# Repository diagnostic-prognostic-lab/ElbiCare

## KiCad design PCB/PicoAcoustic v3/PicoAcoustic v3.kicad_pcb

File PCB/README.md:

# PCB PikoAkustik v3

Revision of **PikoAkustik v2**. Focus: audio quality for audiometry, battery efficiency, and safety.

## Summary

- MCU: STM32F303 → **STM32L4**
- Audio: MAX98357A (Class-D, mono) → **ES8388** (stereo codec: DAC + headphone driver + ADC)
- 5V booster removed
- Relay used for safety and self-test, not for left/right selection
- Main power switch fixed (no leakage current when OFF)

## Changes by block

### Audio
- MAX98357A replaced with **ES8388**
  - Analog output (not PWM), lower noise
  - Stereo: left/right ear selected via I2S data, no relay needed
  - Built-in ADC for calibration self-test
- Audio data 16-bit → **24-bit**
- Added **47 µF coupling capacitors** on LOUT1/ROUT1
- Added **attenuator** (series R + shunt R) per channel: safer maximum level, more accurate low levels
- TRS jack: Tip = L, Ring = R, **Sleeve = GND**
- Removed: L1/L2, speaker filter, MAX98357A gain/SD_MODE setting

### Relay
- G5V-1 (5V coil) → **Omron G6K-2F-Y DC3** (DPDT, 3V coil)
- New function (fail-safe):
  - Relay OFF (default): output to **32 Ω dummy load** + ADC → headphone disconnected, anti-pop, self-test
  - Relay ON: output to headphone (during test)
- Coil powered from 3V3_STM, driven by 2N7002 with B5819W flyback diode

### Power
- **Audio Relay Booster removed** (MCP1640 / MT3608 and related parts)
- Main power switch:
  - Comparator Q3/Q5 (AO3401A) → **BCM857BS** (matched dual PNP)
  - R62/R63 10k → **100k**
  - SW10 moved **before** the ideal diode (VBAT) and **before** D10 (VDDUSB) → near-zero leakage when OFF
- 3 separate AP2112K-3.3 LDOs: STM32, ESP32, codec
- Codec rail: 0 Ω at input (can be replaced with ferrite bead), optional EN from GPIO (DNP)
- L3 (in parallel with LDO) removed
- Label fix: capacitors "4.7uH" → **4.7uF**

### MCU and connectivity
- STM32F303RB → **STM32L4** (SAI for I2S + MCLK, I2C to codec)
- ESP32: added **CH340C USB-UART** + auto-reset (2 NPN), via the charging USB port
- Reset/boot buttons kept (smaller size)
- microSD and SSD1306 OLED unchanged

## Notes

- Dummy load matches the headphone impedance in use (currently 32 Ω, JBL Tune 500)
- Attenuator values are calculated from headphone sensitivity and target maximum level
- Acoustic calibration per headphone is still required; the ADC self-test only checks the electrical path

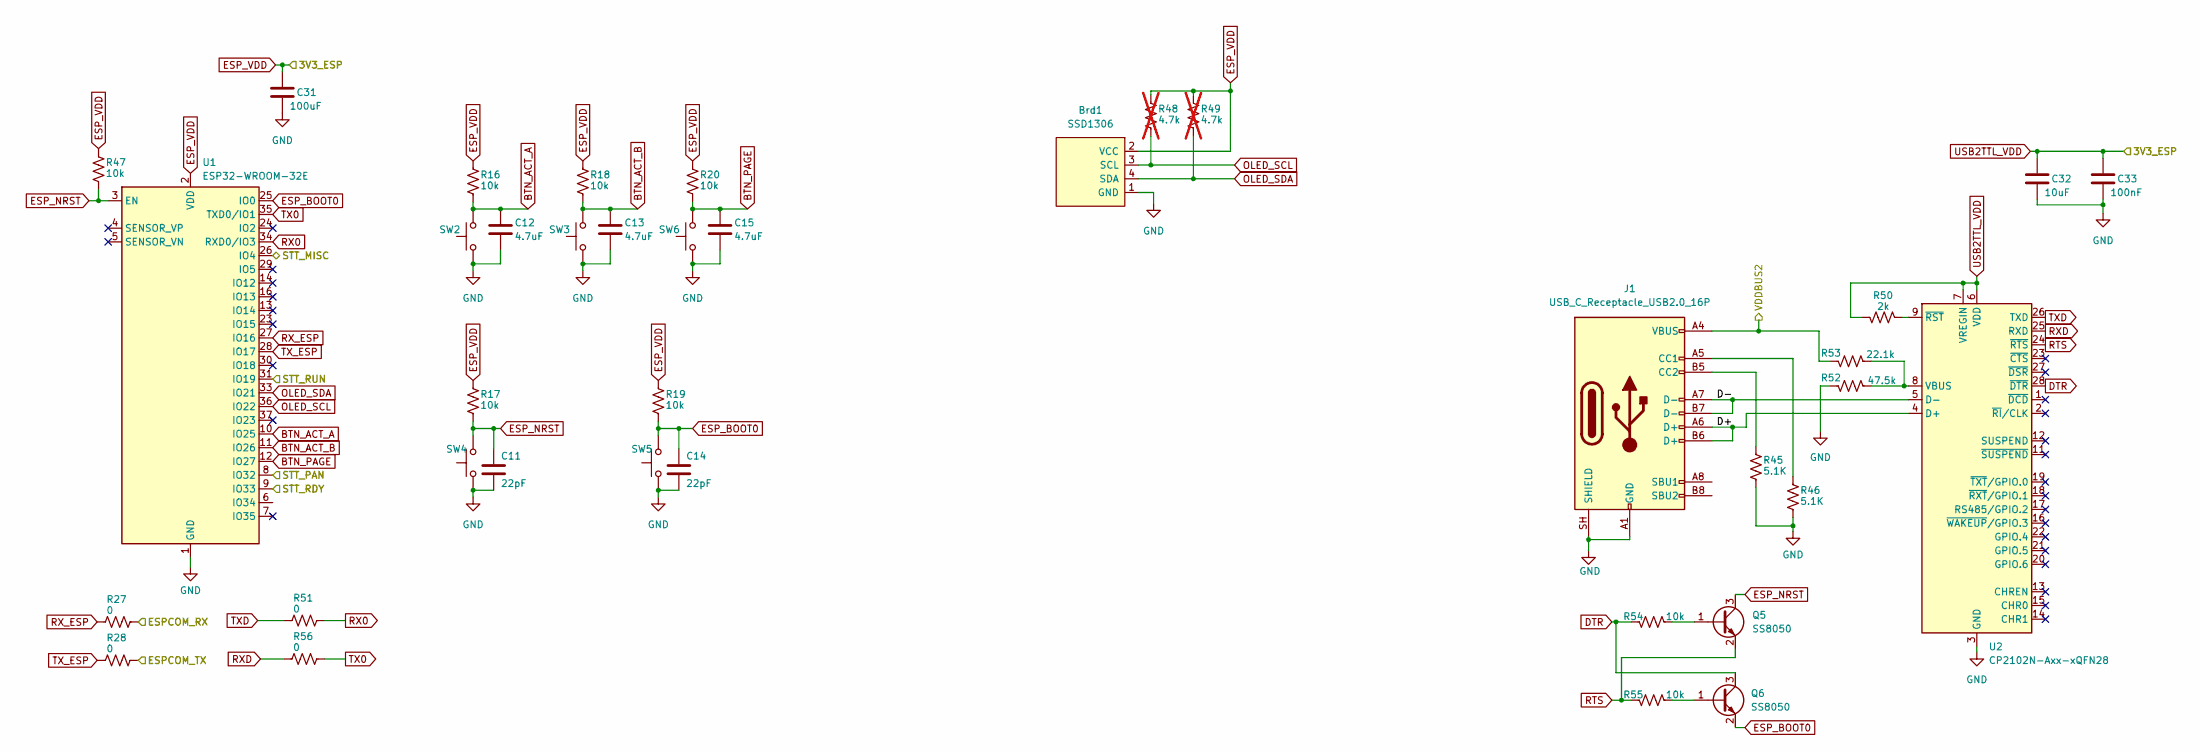
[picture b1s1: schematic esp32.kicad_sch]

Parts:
Brd1: SSD1306; LCD_OLED_128X64_1.3_I2C
C11, C14: 22pF; C_0603_1608Metric
C12, C13, C15: 4.7uF; C_0603_1608Metric
C31: 100uF; C_0603_1608Metric
C32: 10uF; C_0805_2012Metric
C33: 100nF; C_0603_1608Metric
J1: USB_C_Receptacle_USB2.0_16P; USB_C_Receptacle_G-Switch_GT-USB-7010ASV
Q5, Q6: SS8050; SOT-23
R16, R17, R18, R19, R20, R47, R54, R55: 10k; R_0603_1608Metric
R27, R28, R51, R56: 0; R_0603_1608Metric
R45, R46: 5.1K; R_0603_1608Metric
R48, R49: 4.7k; R_0603_1608Metric; not fitted
R50: 2k; R_0603_1608Metric
R52: 47.5k; R_0603_1608Metric
R53: 22.1k; R_0603_1608Metric
SW2, SW3, SW4, SW5, SW6: SW_Push; SW_PUSH_6mm_H13mm
U1: ESP32-WROOM-32E; ESP32-WROOM-32D
U2: CP2102N-Axx-xQFN28; QFN-28-1EP_5x5mm_P0.5mm_EP3.25x3.25mm_ThermalVias

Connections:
/ESP32/D+: J1.A6 (D+), J1.B6 (D+), U2.4 (D+)
/ESP32/D-: J1.A7 (D-), J1.B7 (D-), U2.5 (D-)
/ESP32/ESPCOM_RX: R27.2; also elsewhere on the board
/ESP32/ESPCOM_TX: R28.2; also elsewhere on the board
/ESP32/STT_MISC: U1.26 (IO4); also elsewhere on the board
/ESP32/STT_PAN: U1.8 (IO32); also elsewhere on the board
/ESP32/STT_RDY: U1.9 (IO33); also elsewhere on the board
/ESP32/STT_RUN: U1.31 (IO19); also elsewhere on the board
/ESP32/VDDBUS2: J1.A4 (VBUS), J1.A9 (VBUS), J1.B4 (VBUS), J1.B9 (VBUS), R53.2; also elsewhere on the board
BTN_ACT_A: C12.1, R16.2, SW2.2, U1.10 (IO25)
BTN_ACT_B: C13.1, R18.2, SW3.2, U1.11 (IO26)
BTN_PAGE: C15.1, R20.2, SW6.2, U1.12 (IO27)
DTR: Q6.3 (C), R54.2, U2.28 (~DTR)
ESP_BOOT0: C14.1, Q6.2 (E), R19.2, SW5.2, U1.25 (IO0)
ESP_NRST: C11.1, Q5.3 (C), R17.2, R47.2, SW4.2, U1.3 (EN)
ESP_VDD: Brd1.2 (VCC), C31.1, C32.1, C33.1, R16.1, R17.1, R18.1, R19.1, R20.1, R47.1, R48.1, R49.1, R50.2, U1.2 (VDD), U2.6 (VDD), U2.7 (VREGIN); also elsewhere on the board
GND: Brd1.1 (GND), C11.2, C12.2, C13.2, C14.2, C15.2, C31.2, C32.2, C33.2, J1.A1 (GND), J1.A12 (GND), J1.B1 (GND), J1.B12 (GND), J1.SH (SHIELD), R45.2, R46.2, R52.2, SW2.1, SW3.1, SW4.1, SW5.1, SW6.1, U1.1 (GND), U1.15 (GND), U1.38 (GND), U1.39 (GND), U2.3 (GND), U2.29 (GND); also elsewhere on the board
unnamed: J1.A5 (CC1), R46.1
unnamed: J1.B5 (CC2), R45.1
unnamed: Q5.1 (B), R54.1
unnamed: Q6.1 (B), R55.1
unnamed: R52.1, R53.1, U2.8 (VBUS)
unnamed: R50.1, U2.9 (~RST)
OLED_SCL: Brd1.3 (SCL), R48.2, U1.36 (IO22)
OLED_SDA: Brd1.4 (SDA), R49.2, U1.33 (IO21)
RTS: Q5.2 (E), R55.2, U2.24 (~RTS)
RX0: R51.2, U1.34 (RXD0/IO3)
RXD: R56.1, U2.25 (RXD)
RX_ESP: R27.1, U1.27 (IO16)
TX0: R56.2, U1.35 (TXD0/IO1)
TXD: R51.1, U2.26 (TXD)
TX_ESP: R28.1, U1.28 (IO17)

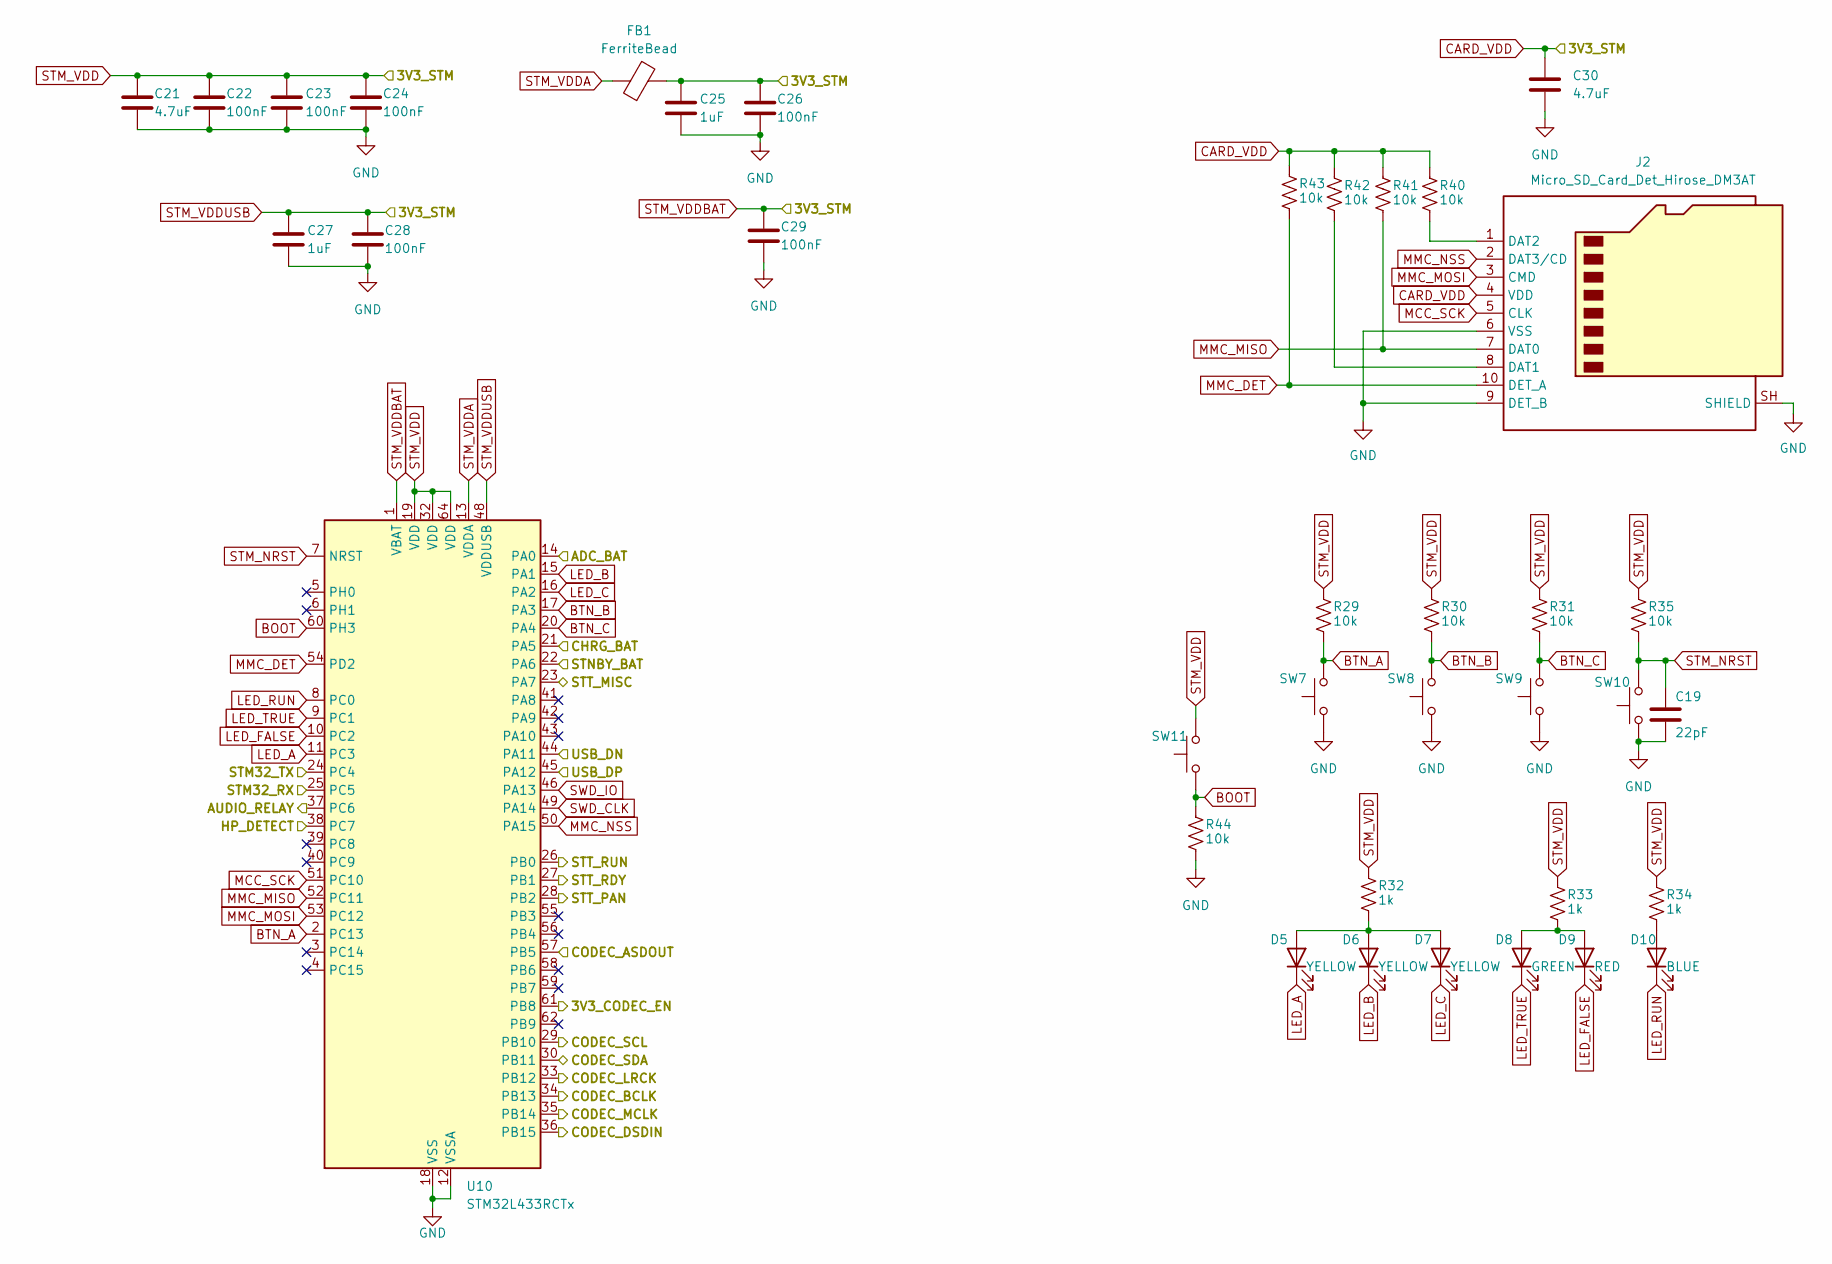
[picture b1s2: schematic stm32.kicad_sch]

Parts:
C19: 22pF; C_0603_1608Metric
C21, C30: 4.7uF; C_0603_1608Metric
C22, C23, C24, C26, C28, C29: 100nF; C_0603_1608Metric
C25, C27: 1uF; C_0603_1608Metric
D5, D6, D7: YELLOW; LED_0603_1608Metric
D8: GREEN; LED_0603_1608Metric
D9: RED; LED_0603_1608Metric
D10: BLUE; LED_0603_1608Metric
FB1: FerriteBead; L_0603_1608Metric
J2: Micro_SD_Card_Det_Hirose_DM3AT; microSD_HC_Hirose_DM3AT-SF-PEJM5
R29, R30, R31, R35, R40, R41, R42, R43, R44: 10k; R_0603_1608Metric
R32, R33, R34: 1k; R_0603_1608Metric
SW7, SW8, SW9, SW10, SW11: SW_Push; SW_PUSH_6mm_H13mm
U10: STM32L433RCTx; LQFP-64_10x10mm_P0.5mm

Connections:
/Analog Line/AUDIO_RELAY: U10.37 (PC6); also elsewhere on the board
/Analog Line/CODEC_ASDOUT: U10.57 (PB5); also elsewhere on the board
/Analog Line/CODEC_DSDIN: U10.36 (PB15); also elsewhere on the board
/Analog Line/CODEC_LRCK: U10.33 (PB12); also elsewhere on the board
/Analog Line/CODEC_MCLK: U10.35 (PB14); also elsewhere on the board
/Analog Line/CODEC_SCL: U10.29 (PB10); also elsewhere on the board
/Analog Line/CODEC_SCLK: U10.34 (PB13); also elsewhere on the board
/Analog Line/CODEC_SDA: U10.30 (PB11); also elsewhere on the board
/Analog Line/HP_DETECT: U10.38 (PC7); also elsewhere on the board
/ESP32/ESPCOM_RX: U10.24 (PC4); also elsewhere on the board
/ESP32/ESPCOM_TX: U10.25 (PC5); also elsewhere on the board
/ESP32/STT_MISC: U10.23 (PA7); also elsewhere on the board
/ESP32/STT_PAN: U10.28 (PB2); also elsewhere on the board
/ESP32/STT_RDY: U10.27 (PB1); also elsewhere on the board
/ESP32/STT_RUN: U10.26 (PB0); also elsewhere on the board
/Power Line/3V3_CODEC_EN: U10.61 (PB8); also elsewhere on the board
/Power Line/STM_DN: U10.44 (PA11); also elsewhere on the board
/Power Line/STM_DP: U10.45 (PA12); also elsewhere on the board
/Power Line/VBAT_SENSE: U10.14 (PA0); also elsewhere on the board
BOOT: R44.1, SW11.1, U10.60 (PH3)
BTN_A: R29.2, SW7.2, U10.2 (PC13)
BTN_B: R30.2, SW8.2, U10.17 (PA3)
BTN_C: R31.2, SW9.2, U10.20 (PA4)
CARD_VDD: C21.1, C22.1, C23.1, C24.1, C25.1, C26.1, C27.1, C28.1, C29.1, C30.1, FB1.2, J2.4 (VDD), R29.1, R30.1, R31.1, R32.1, R33.1, R34.1, R35.1, R40.1, R41.1, R42.1, R43.1, SW11.2, U10.1 (VBAT), U10.19 (VDD), U10.32 (VDD), U10.48 (VDDUSB), U10.64 (VDD); also elsewhere on the board
CHRG: U10.21 (PA5); also elsewhere on the board
GND: C19.2, C21.2, C22.2, C23.2, C24.2, C25.2, C26.2, C27.2, C28.2, C29.2, C30.2, J2.6 (VSS), J2.9 (DET_B), J2.SH (SHIELD), R44.2, SW7.1, SW8.1, SW9.1, SW10.1, U10.12 (VSSA), U10.18 (VSS), U10.31 (VSS), U10.47 (VSS), U10.63 (VSS); also elsewhere on the board
LED_A: D5.1 (K), U10.11 (PC3)
LED_B: D6.1 (K), U10.15 (PA1)
LED_C: D7.1 (K), U10.16 (PA2)
LED_FALSE: D9.1 (K), U10.10 (PC2)
LED_RUN: D10.1 (K), U10.8 (PC0)
LED_TRUE: D8.1 (K), U10.9 (PC1)
MCC_SCK: J2.5 (CLK), U10.51 (PC10)
MMC_DET: J2.10 (DET_A), R43.2, U10.54 (PD2)
MMC_MISO: J2.7 (DAT0), R41.2, U10.52 (PC11)
MMC_MOSI: J2.3 (CMD), U10.53 (PC12)
MMC_NSS: J2.2 (DAT3/CD), U10.50 (PA15)
unnamed: D5.2 (A), D6.2 (A), D7.2 (A), R32.2
unnamed: D8.2 (A), D9.2 (A), R33.2
unnamed: D10.2 (A), R34.2
unnamed: J2.8 (DAT1), R42.2
unnamed: J2.1 (DAT2), R40.2
STM_NRST: C19.1, R35.2, SW10.2, U10.7 (NRST)
STM_VDDA: FB1.1, U10.13 (VDDA)
STNBY: U10.22 (PA6); also elsewhere on the board
SWD_CLK: U10.49 (PA14)
SWD_IO: U10.46 (PA13)

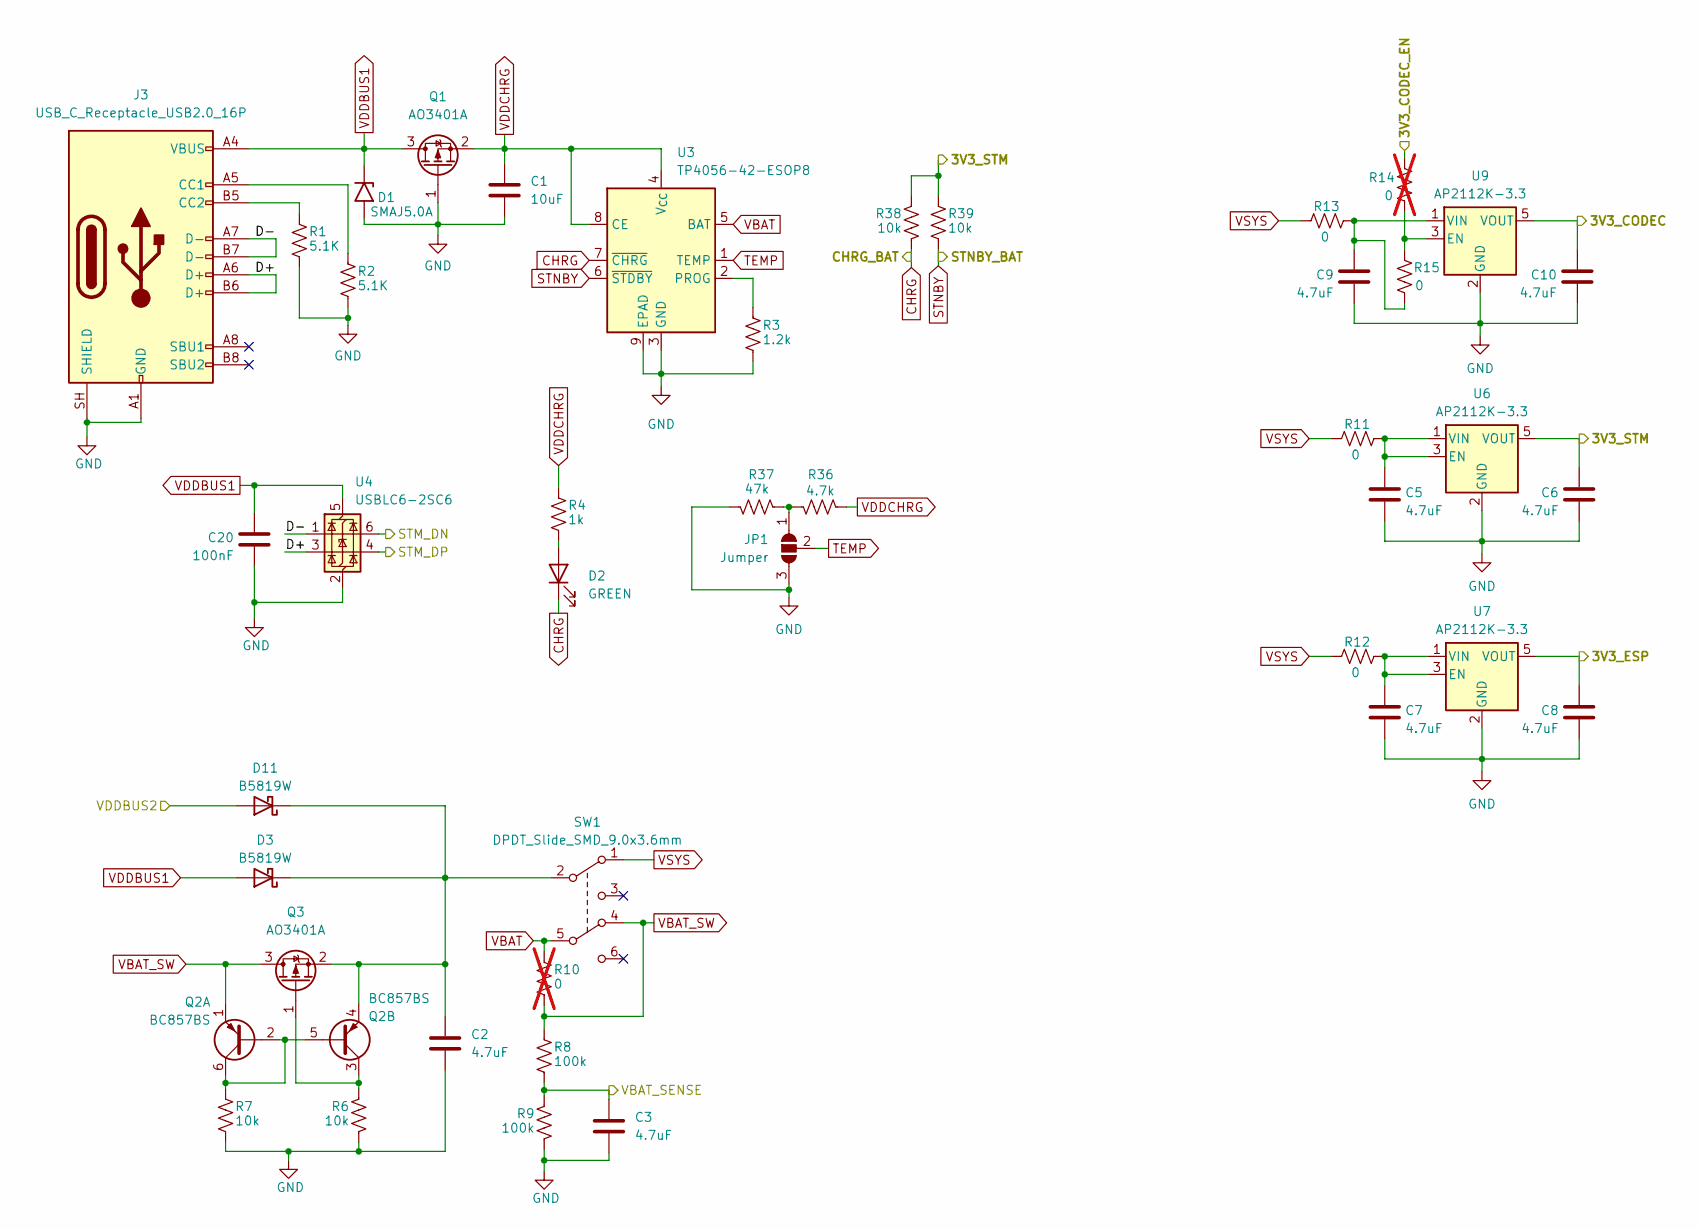
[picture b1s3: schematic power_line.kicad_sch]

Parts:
C1: 10uF; C_0603_1608Metric
C2, C3, C5, C6, C7, C8, C9, C10: 4.7uF; C_0603_1608Metric
C20: 100nF; C_0603_1608Metric
D1: SMAJ5.0A; D_SMA
D2: GREEN; LED_0603_1608Metric
D3, D11: B5819W; D_SMA
J3: USB_C_Receptacle_USB2.0_16P; USB_C_Receptacle_G-Switch_GT-USB-7010ASV
JP1: Jumper; SolderJumper-3_P1.3mm_Open_RoundedPad1.0x1.5mm_NumberLabels
Q1, Q3: AO3401A; SOT-23
Q2: BC857BS; SOT-363_SC-70-6
R1, R2: 5.1K; R_0603_1608Metric
R3: 1.2k; R_0603_1608Metric
R4: 1k; R_0603_1608Metric
R6, R7, R38, R39: 10k; R_0603_1608Metric
R8, R9: 100k; R_0603_1608Metric
R10, R14: 0; R_0603_1608Metric; not fitted
R11, R12, R13, R15: 0; R_0603_1608Metric
R36: 4.7k; R_0603_1608Metric
R37: 47k; R_0603_1608Metric
SW1: DPDT_Slide_SMD_9.0x3.6mm; SW_Push_2P2T_Toggle_CK_PVA2xxH1xxxxxxV2
U3: TP4056-42-ESOP8; SOIC-8-1EP_3.9x4.9mm_P1.27mm_EP2.41x3.3mm_ThermalVias
U4: USBLC6-2SC6; SOT-23-6
U6, U7, U9: AP2112K-3.3; SOT-23-5

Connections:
/ESP32/VDDBUS2: D11.2 (A); also elsewhere on the board
/Power Line/3V3_CODEC_EN: R14.2; also elsewhere on the board
/Power Line/D+: J3.A6 (D+), J3.B6 (D+), U4.3 (I/O2)
/Power Line/D-: J3.A7 (D-), J3.B7 (D-), U4.1 (I/O1)
/Power Line/STM_DN: U4.6 (I/O1); also elsewhere on the board
/Power Line/STM_DP: U4.4 (I/O2); also elsewhere on the board
/Power Line/VBAT_SENSE: C3.1, R8.2, R9.1; also elsewhere on the board
AVDD: C10.1, U9.5 (VOUT); also elsewhere on the board
CARD_VDD: C6.1, R38.1, R39.1, U6.5 (VOUT); also elsewhere on the board
CHRG: D2.1 (K), R38.2, U3.7 (~CHRG); also elsewhere on the board
ESP_VDD: C8.1, U7.5 (VOUT); also elsewhere on the board
GND: C1.2, C2.2, C3.2, C5.2, C6.2, C7.2, C8.2, C9.2, C10.2, C20.2, D1.2 (A2), J3.A1 (GND), J3.A12 (GND), J3.B1 (GND), J3.B12 (GND), J3.SH (SHIELD), JP1.3 (B), Q1.1 (G), R1.2, R2.2, R3.2, R6.2, R7.2, R9.2, R37.2, U3.3 (GND), U3.9 (EPAD), U4.2 (GND), U6.2 (GND), U7.2 (GND), U9.2 (GND); also elsewhere on the board
unnamed: D2.2 (A), R4.2
unnamed: C2.1, D3.1 (K), D11.1 (K), Q2.4 (E2), Q3.2 (S), SW1.2 (B)
unnamed: J3.A5 (CC1), R2.1
unnamed: J3.B5 (CC2), R1.1
unnamed: JP1.1 (A), R36.2, R37.1
unnamed: Q2.2 (B1), Q2.5 (B2), Q2.6 (C1), R7.1
unnamed: Q2.3 (C2), Q3.1 (G), R6.1
unnamed: R3.1, U3.2 (PROG)
unnamed: C5.1, R11.2, U6.1 (VIN), U6.3 (EN)
unnamed: C7.1, R12.2, U7.1 (VIN), U7.3 (EN)
unnamed: R14.1, R15.2, U9.3 (EN)
unnamed: C9.1, R13.2, R15.1, U9.1 (VIN)
STNBY: R39.2, U3.6 (~STDBY); also elsewhere on the board
TEMP: JP1.2 (C), U3.1 (TEMP)
VBAT: R10.1, SW1.5 (B), U3.5 (BAT)
VBAT_SW: Q2.1 (E1), Q3.3 (D), R8.1, R10.2, SW1.4 (A)
VDDBUS1: C20.1, D1.1 (A1), D3.2 (A), J3.A4 (VBUS), J3.A9 (VBUS), J3.B4 (VBUS), J3.B9 (VBUS), Q1.3 (D), U4.5 (VBUS)
VDDCHRG: C1.1, Q1.2 (S), R4.1, R36.1, U3.4 (V_{CC}), U3.8 (CE)
VSYS: R11.1, R12.1, R13.1, SW1.1 (A)

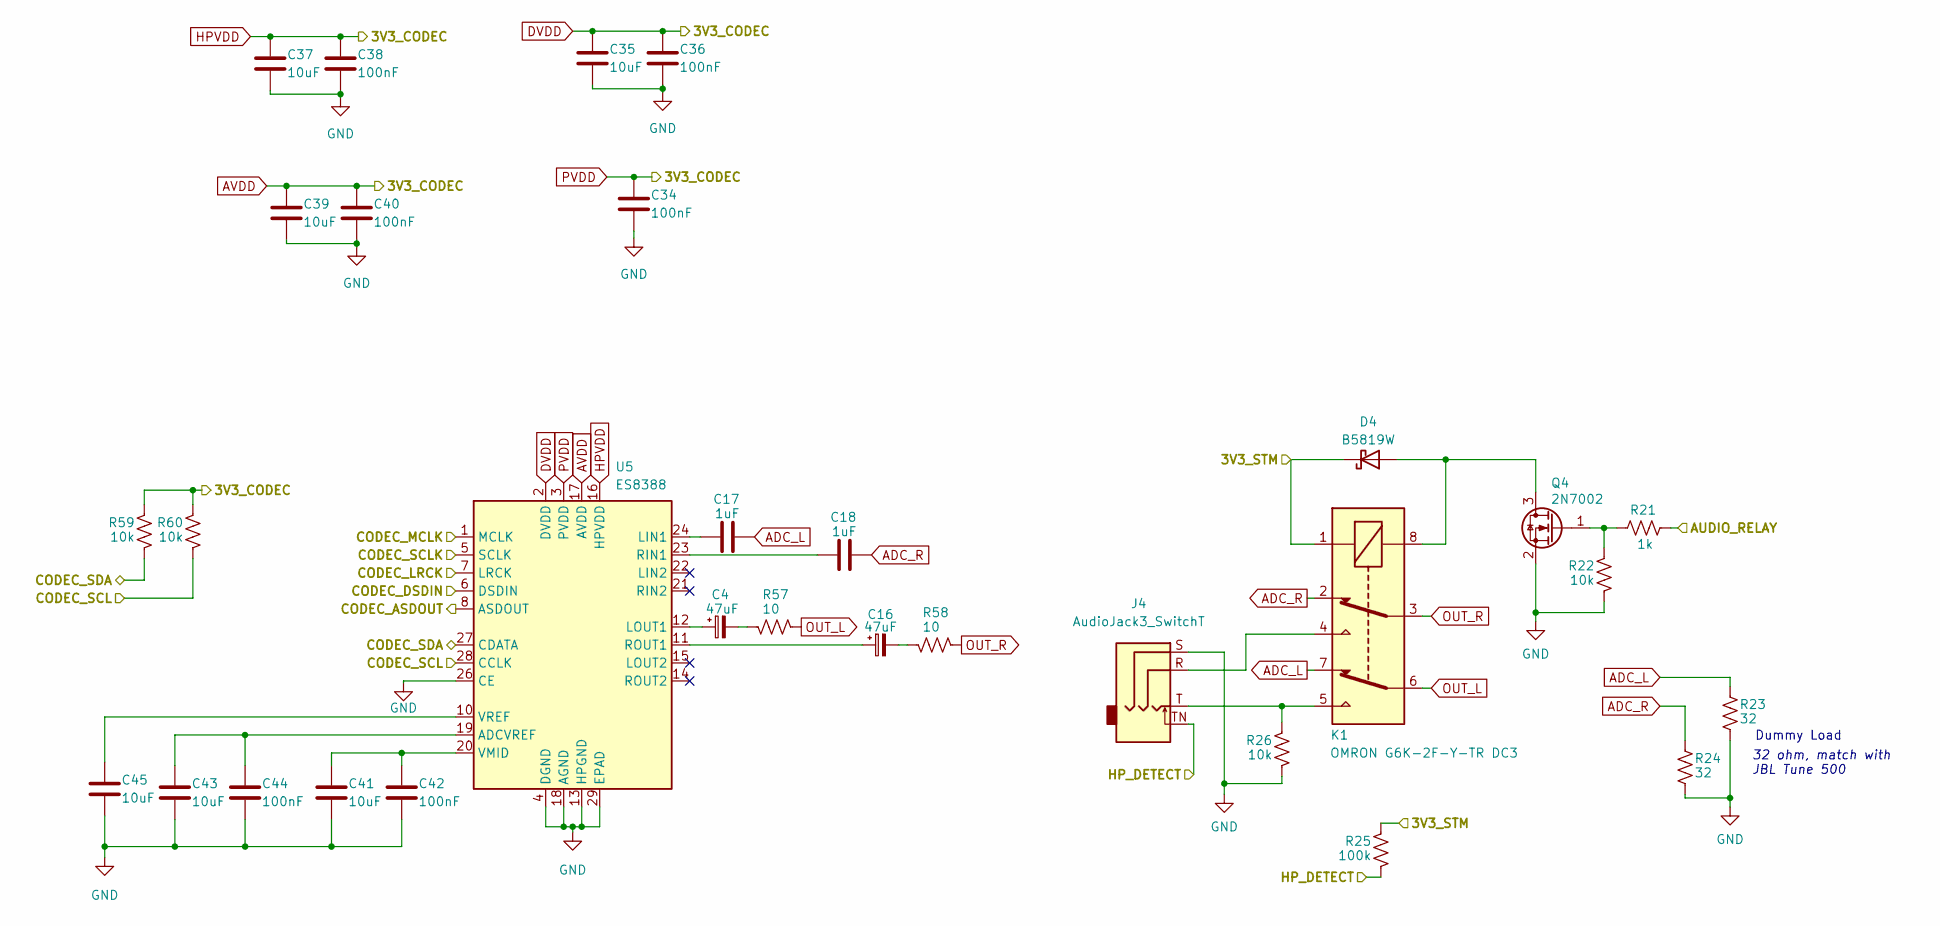
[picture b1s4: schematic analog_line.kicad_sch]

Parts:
C4, C16: 47uF; CP_Elec_5x5.7
C17, C18: 1uF; C_0603_1608Metric
C34, C36, C38, C40, C42, C44: 100nF; C_0603_1608Metric
C35, C37, C39, C41, C43, C45: 10uF; C_0805_2012Metric
D4: B5819W; D_SMA
J4: AudioJack3_SwitchT; Jack_3.5mm_CUI_SJ-3524-SMT_Horizontal
K1: OMRON G6K-2F-Y-TR DC3; Relay_DPDT_Omron_G6K-2F-Y
Q4: 2N7002; SOT-23
R21: 1k; R_0603_1608Metric
R22, R26, R59, R60: 10k; R_0603_1608Metric
R23, R24: 32; R_0603_1608Metric
R25: 100k; R_0603_1608Metric
R57, R58: 10; R_0603_1608Metric
U5: ES8388; QFN-28-1EP_4x4mm_P0.45mm_EP2.6x2.6mm

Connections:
/Analog Line/AUDIO_RELAY: R21.2; also elsewhere on the board
/Analog Line/CODEC_ASDOUT: U5.8 (ASDOUT); also elsewhere on the board
/Analog Line/CODEC_DSDIN: U5.6 (DSDIN); also elsewhere on the board
/Analog Line/CODEC_LRCK: U5.7 (LRCK); also elsewhere on the board
/Analog Line/CODEC_MCLK: U5.1 (MCLK); also elsewhere on the board
/Analog Line/CODEC_SCL: R60.2, U5.28 (CCLK); also elsewhere on the board
/Analog Line/CODEC_SCLK: U5.5 (SCLK); also elsewhere on the board
/Analog Line/CODEC_SDA: R59.2, U5.27 (CDATA); also elsewhere on the board
/Analog Line/HP_DETECT: J4.TN, R25.2; also elsewhere on the board
ADC_L: C17.2, K1.7, R23.1
ADC_R: C18.2, K1.2, R24.1
AVDD: C34.1, C35.1, C36.1, C37.1, C38.1, C39.1, C40.1, R59.1, R60.1, U5.2 (DVDD), U5.3 (PVDD), U5.16 (HPVDD), U5.17 (AVDD); also elsewhere on the board
CARD_VDD: D4.1 (K), K1.1, R25.1; also elsewhere on the board
GND: C34.2, C35.2, C36.2, C37.2, C38.2, C39.2, C40.2, C41.2, C42.2, C43.2, C44.2, C45.2, J4.S, Q4.2 (S), R22.2, R23.2, R24.2, R26.2, U5.4 (DGND), U5.13 (HPGND), U5.18 (AGND), U5.26 (CE), U5.29 (EPAD); also elsewhere on the board
unnamed: C4.2, R57.2
unnamed: C16.2, R58.2
unnamed: D4.2 (A), K1.8, Q4.3 (D)
unnamed: J4.R, K1.4
unnamed: J4.T, K1.5, R26.1
unnamed: Q4.1 (G), R21.1, R22.1
unnamed: C43.1, C44.1, U5.19 (ADCVREF)
unnamed: C17.1, U5.24 (LIN1)
unnamed: C4.1, U5.12 (LOUT1)
unnamed: C18.1, U5.23 (RIN1)
unnamed: C16.1, U5.11 (ROUT1)
unnamed: C41.1, C42.1, U5.20 (VMID)
unnamed: C45.1, U5.10 (VREF)
OUT_L: K1.6, R57.1
OUT_R: K1.3, R58.1

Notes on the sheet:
32 ohm, match with JBL Tune 500
Dummy Load

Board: 2 copper layers, 149 parts (0 on the bottom side), 108 nets, no tracks yet.
